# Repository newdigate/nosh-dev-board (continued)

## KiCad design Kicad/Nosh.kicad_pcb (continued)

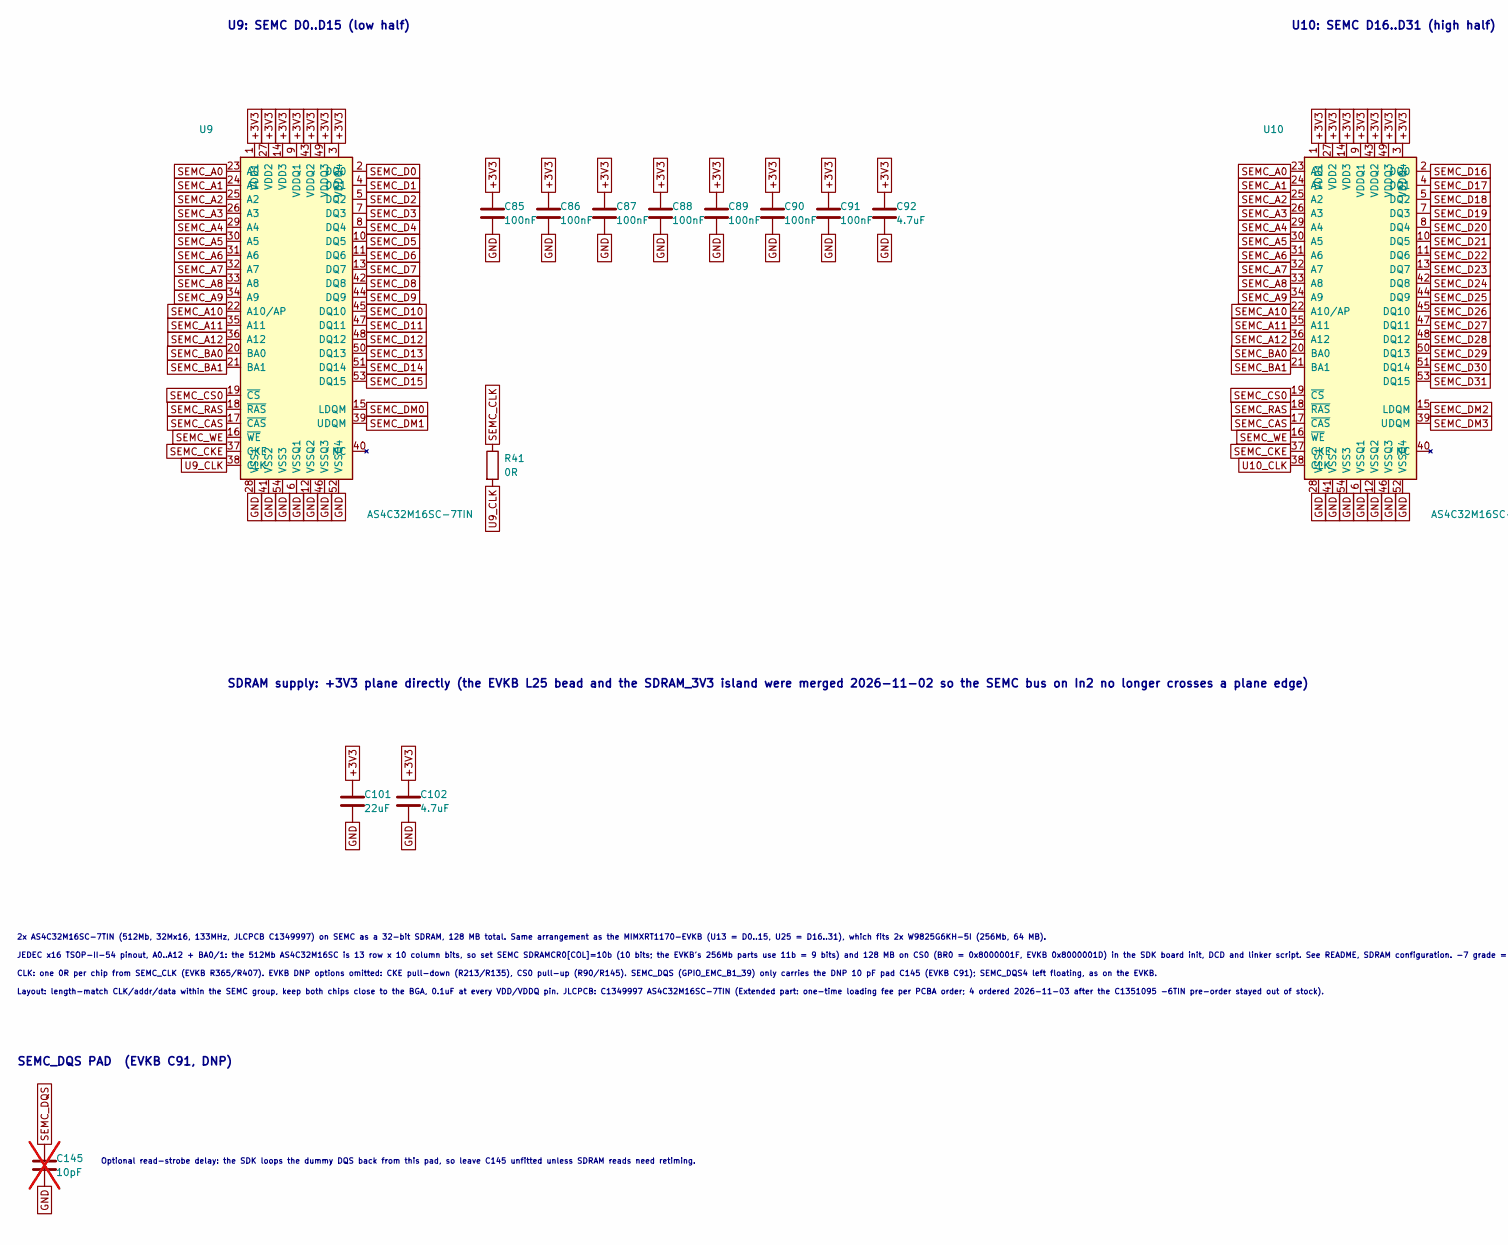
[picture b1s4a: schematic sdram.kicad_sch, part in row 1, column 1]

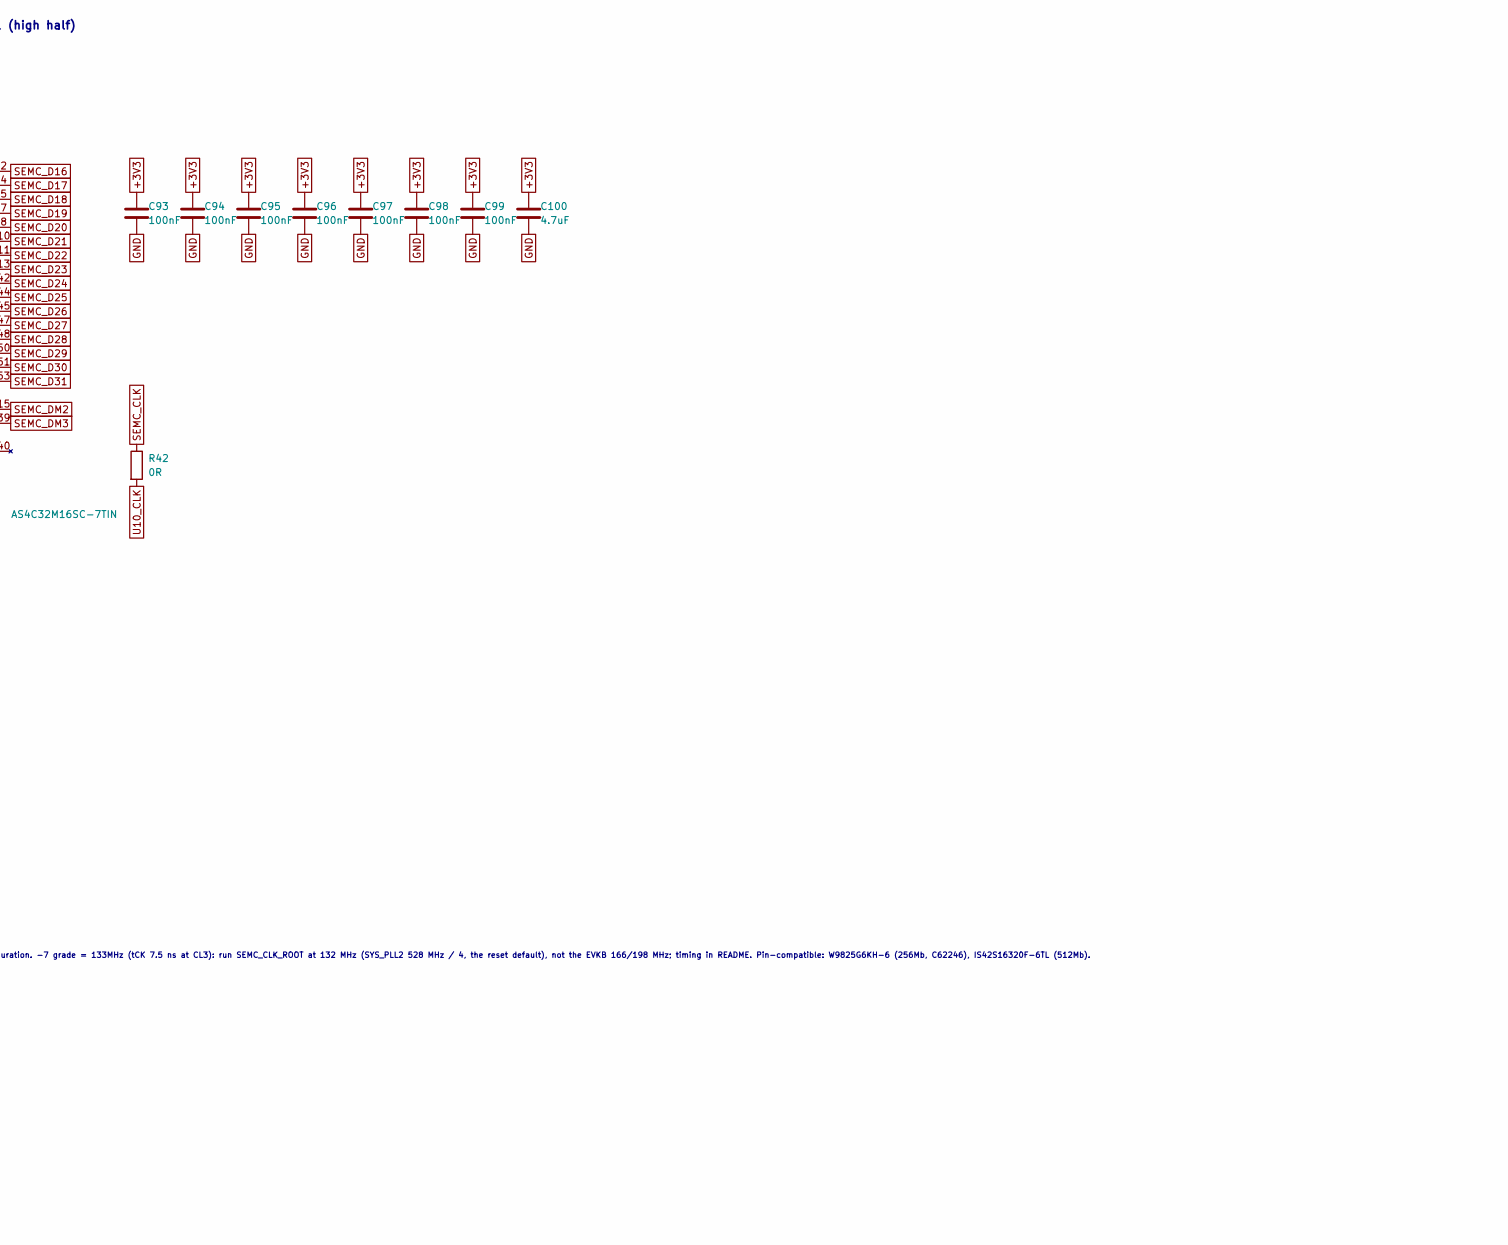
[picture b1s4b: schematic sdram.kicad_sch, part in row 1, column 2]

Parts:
C85, C86, C87, C88, C89, C90, C91, C94, C95, C96, C97, C98, C99: 100nF; C_0402_1005Metric_JLC; MPN CL05B104KO5NNNC; LCSC C1525
C92, C100, C102: 4.7uF; C_0603_1608Metric; MPN CL10A475KO8NNNC; LCSC C19666
C93: 100nF; C_0402_1005Metric_ViP; MPN CL05B104KO5NNNC; LCSC C1525
C101: 22uF; C_0805_2012Metric; MPN CL21A226MAQNNNE; LCSC C45783
C145: 10pF; C_0402_1005Metric_JLC; MPN 0402CG100J500NT; LCSC C1545; not fitted
R41, R42: 0R; R_0402_1005Metric_JLC; MPN 0402WGF0000TCE; LCSC C17168
U9, U10: AS4C32M16SC-7TIN; TSOP-II-54_22.2x10.16mm_P0.8mm; MPN AS4C32M16SC-7TIN; LCSC C1349997

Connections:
+3V3: C85.1, C86.1, C87.1, C88.1, C89.1, C90.1, C91.1, C92.1, C93.1, C94.1, C95.1, C96.1, C97.1, C98.1, C99.1, C100.1, C101.1, C102.1, U9.1 (VDD1), U9.3 (VDDQ4), U9.9 (VDDQ1), U9.14 (VDD3), U9.27 (VDD2), U9.43 (VDDQ2), U9.49 (VDDQ3), U10.1 (VDD1), U10.3 (VDDQ4), U10.9 (VDDQ1), U10.14 (VDD3), U10.27 (VDD2), U10.43 (VDDQ2), U10.49 (VDDQ3); also elsewhere on the board
GND: C85.2, C86.2, C87.2, C88.2, C89.2, C90.2, C91.2, C92.2, C93.2, C94.2, C95.2, C96.2, C97.2, C98.2, C99.2, C100.2, C101.2, C102.2, C145.2, U9.6 (VSSQ1), U9.12 (VSSQ2), U9.28 (VSS1), U9.41 (VSS2), U9.46 (VSSQ3), U9.52 (VSSQ4), U9.54 (VSS3), U10.6 (VSSQ1), U10.12 (VSSQ2), U10.28 (VSS1), U10.41 (VSS2), U10.46 (VSSQ3), U10.52 (VSSQ4), U10.54 (VSS3); also elsewhere on the board
SEMC_A0: U9.23 (A0), U10.23 (A0); also elsewhere on the board
SEMC_A1: U9.24 (A1), U10.24 (A1); also elsewhere on the board
SEMC_A2: U9.25 (A2), U10.25 (A2); also elsewhere on the board
SEMC_A3: U9.26 (A3), U10.26 (A3); also elsewhere on the board
SEMC_A4: U9.29 (A4), U10.29 (A4); also elsewhere on the board
SEMC_A5: U9.30 (A5), U10.30 (A5); also elsewhere on the board
SEMC_A6: U9.31 (A6), U10.31 (A6); also elsewhere on the board
SEMC_A7: U9.32 (A7), U10.32 (A7); also elsewhere on the board
SEMC_A8: U9.33 (A8), U10.33 (A8); also elsewhere on the board
SEMC_A9: U9.34 (A9), U10.34 (A9); also elsewhere on the board
SEMC_A10: U9.22 (A10/AP), U10.22 (A10/AP); also elsewhere on the board
SEMC_A11: U9.35 (A11), U10.35 (A11); also elsewhere on the board
SEMC_A12: U9.36 (A12), U10.36 (A12); also elsewhere on the board
SEMC_BA0: U9.20 (BA0), U10.20 (BA0); also elsewhere on the board
SEMC_BA1: U9.21 (BA1), U10.21 (BA1); also elsewhere on the board
SEMC_CAS: U9.17 (~CAS), U10.17 (~CAS); also elsewhere on the board
SEMC_CKE: U9.37 (CKE), U10.37 (CKE); also elsewhere on the board
SEMC_CLK: R41.1, R42.1; also elsewhere on the board
SEMC_CS0: U9.19 (~CS), U10.19 (~CS); also elsewhere on the board
SEMC_D0: U9.2 (DQ0); also elsewhere on the board
SEMC_D1: U9.4 (DQ1); also elsewhere on the board
SEMC_D2: U9.5 (DQ2); also elsewhere on the board
SEMC_D3: U9.7 (DQ3); also elsewhere on the board
SEMC_D4: U9.8 (DQ4); also elsewhere on the board
SEMC_D5: U9.10 (DQ5); also elsewhere on the board
SEMC_D6: U9.11 (DQ6); also elsewhere on the board
SEMC_D7: U9.13 (DQ7); also elsewhere on the board
SEMC_D8: U9.42 (DQ8); also elsewhere on the board
SEMC_D9: U9.44 (DQ9); also elsewhere on the board
SEMC_D10: U9.45 (DQ10); also elsewhere on the board
SEMC_D11: U9.47 (DQ11); also elsewhere on the board
SEMC_D12: U9.48 (DQ12); also elsewhere on the board
SEMC_D13: U9.50 (DQ13); also elsewhere on the board
SEMC_D14: U9.51 (DQ14); also elsewhere on the board
SEMC_D15: U9.53 (DQ15); also elsewhere on the board
SEMC_D16: U10.2 (DQ0); also elsewhere on the board
SEMC_D17: U10.4 (DQ1); also elsewhere on the board
SEMC_D18: U10.5 (DQ2); also elsewhere on the board
SEMC_D19: U10.7 (DQ3); also elsewhere on the board
SEMC_D20: U10.8 (DQ4); also elsewhere on the board
SEMC_D21: U10.10 (DQ5); also elsewhere on the board
SEMC_D22: U10.11 (DQ6); also elsewhere on the board
SEMC_D23: U10.13 (DQ7); also elsewhere on the board
SEMC_D24: U10.42 (DQ8); also elsewhere on the board
SEMC_D25: U10.44 (DQ9); also elsewhere on the board
SEMC_D26: U10.45 (DQ10); also elsewhere on the board
SEMC_D27: U10.47 (DQ11); also elsewhere on the board
SEMC_D28: U10.48 (DQ12); also elsewhere on the board
SEMC_D29: U10.50 (DQ13); also elsewhere on the board
SEMC_D30: U10.51 (DQ14); also elsewhere on the board
SEMC_D31: U10.53 (DQ15); also elsewhere on the board
SEMC_DM0: U9.15 (LDQM); also elsewhere on the board
SEMC_DM1: U9.39 (UDQM); also elsewhere on the board
SEMC_DM2: U10.15 (LDQM); also elsewhere on the board
SEMC_DM3: U10.39 (UDQM); also elsewhere on the board
SEMC_DQS: C145.1; also elsewhere on the board
SEMC_RAS: U9.18 (~RAS), U10.18 (~RAS); also elsewhere on the board
SEMC_WE: U9.16 (~WE), U10.16 (~WE); also elsewhere on the board
U9_CLK: R41.2, U9.38 (CLK)
U10_CLK: R42.2, U10.38 (CLK)

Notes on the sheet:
SDRAM supply: +3V3 plane directly (the EVKB L25 bead and the SDRAM_3V3 island were merged 2026-11-02 so the SEMC bus on In2 no longer crosses a plane edge)
SEMC_DQS PAD (EVKB C91, DNP)
Layout: length-match CLK/addr/data within the SEMC group, keep both chips close to the BGA, 0.1uF at every VDD/VDDQ pin. JLCPCB: C1349997 AS4C32M16SC-7TIN (Extended part: one-time loading fee per PCBA order; 4 ordered 2026-11-03 after the C1351095 -6TIN pre-order stayed out of stock).
U9: SEMC D0..D15 (low half)
CLK: one 0R per chip from SEMC_CLK (EVKB R365/R407). EVKB DNP options omitted: CKE pull-down (R213/R135), CS0 pull-up (R90/R145). SEMC_DQS (GPIO_EMC_B1_39) only carries the DNP 10 pF pad C145 (EVKB C91); SEMC_DQS4 left floating, as on the EVKB.
JEDEC x16 TSOP-II-54 pinout, A0..A12 + BA0/1: the 512Mb AS4C32M16SC is 13 row x 10 column bits, so set SEMC SDRAMCR0[COL]=10b (10 bits; the EVKB's 256Mb parts use 11b = 9 bits) and 128 MB on CS0 (BR0 = 0x8000001F, EVKB 0x8000001D) in the SDK board init, DCD and linker script. See README, SDRAM conf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
U10: SEMC D16..D31 (high half)
2x AS4C32M16SC-7TIN (512Mb, 32Mx16, 133MHz, JLCPCB C1349997) on SEMC as a 32-bit SDRAM, 128 MB total. Same arrangement as the MIMXRT1170-EVKB (U13 = D0..15, U25 = D16..31), which fits 2x W9825G6KH-5I (256Mb, 64 MB).
Optional read-strobe delay: the SDK loops the dummy DQS back from this pad, so leave C145 unfitted unless SDRAM reads need retiming.

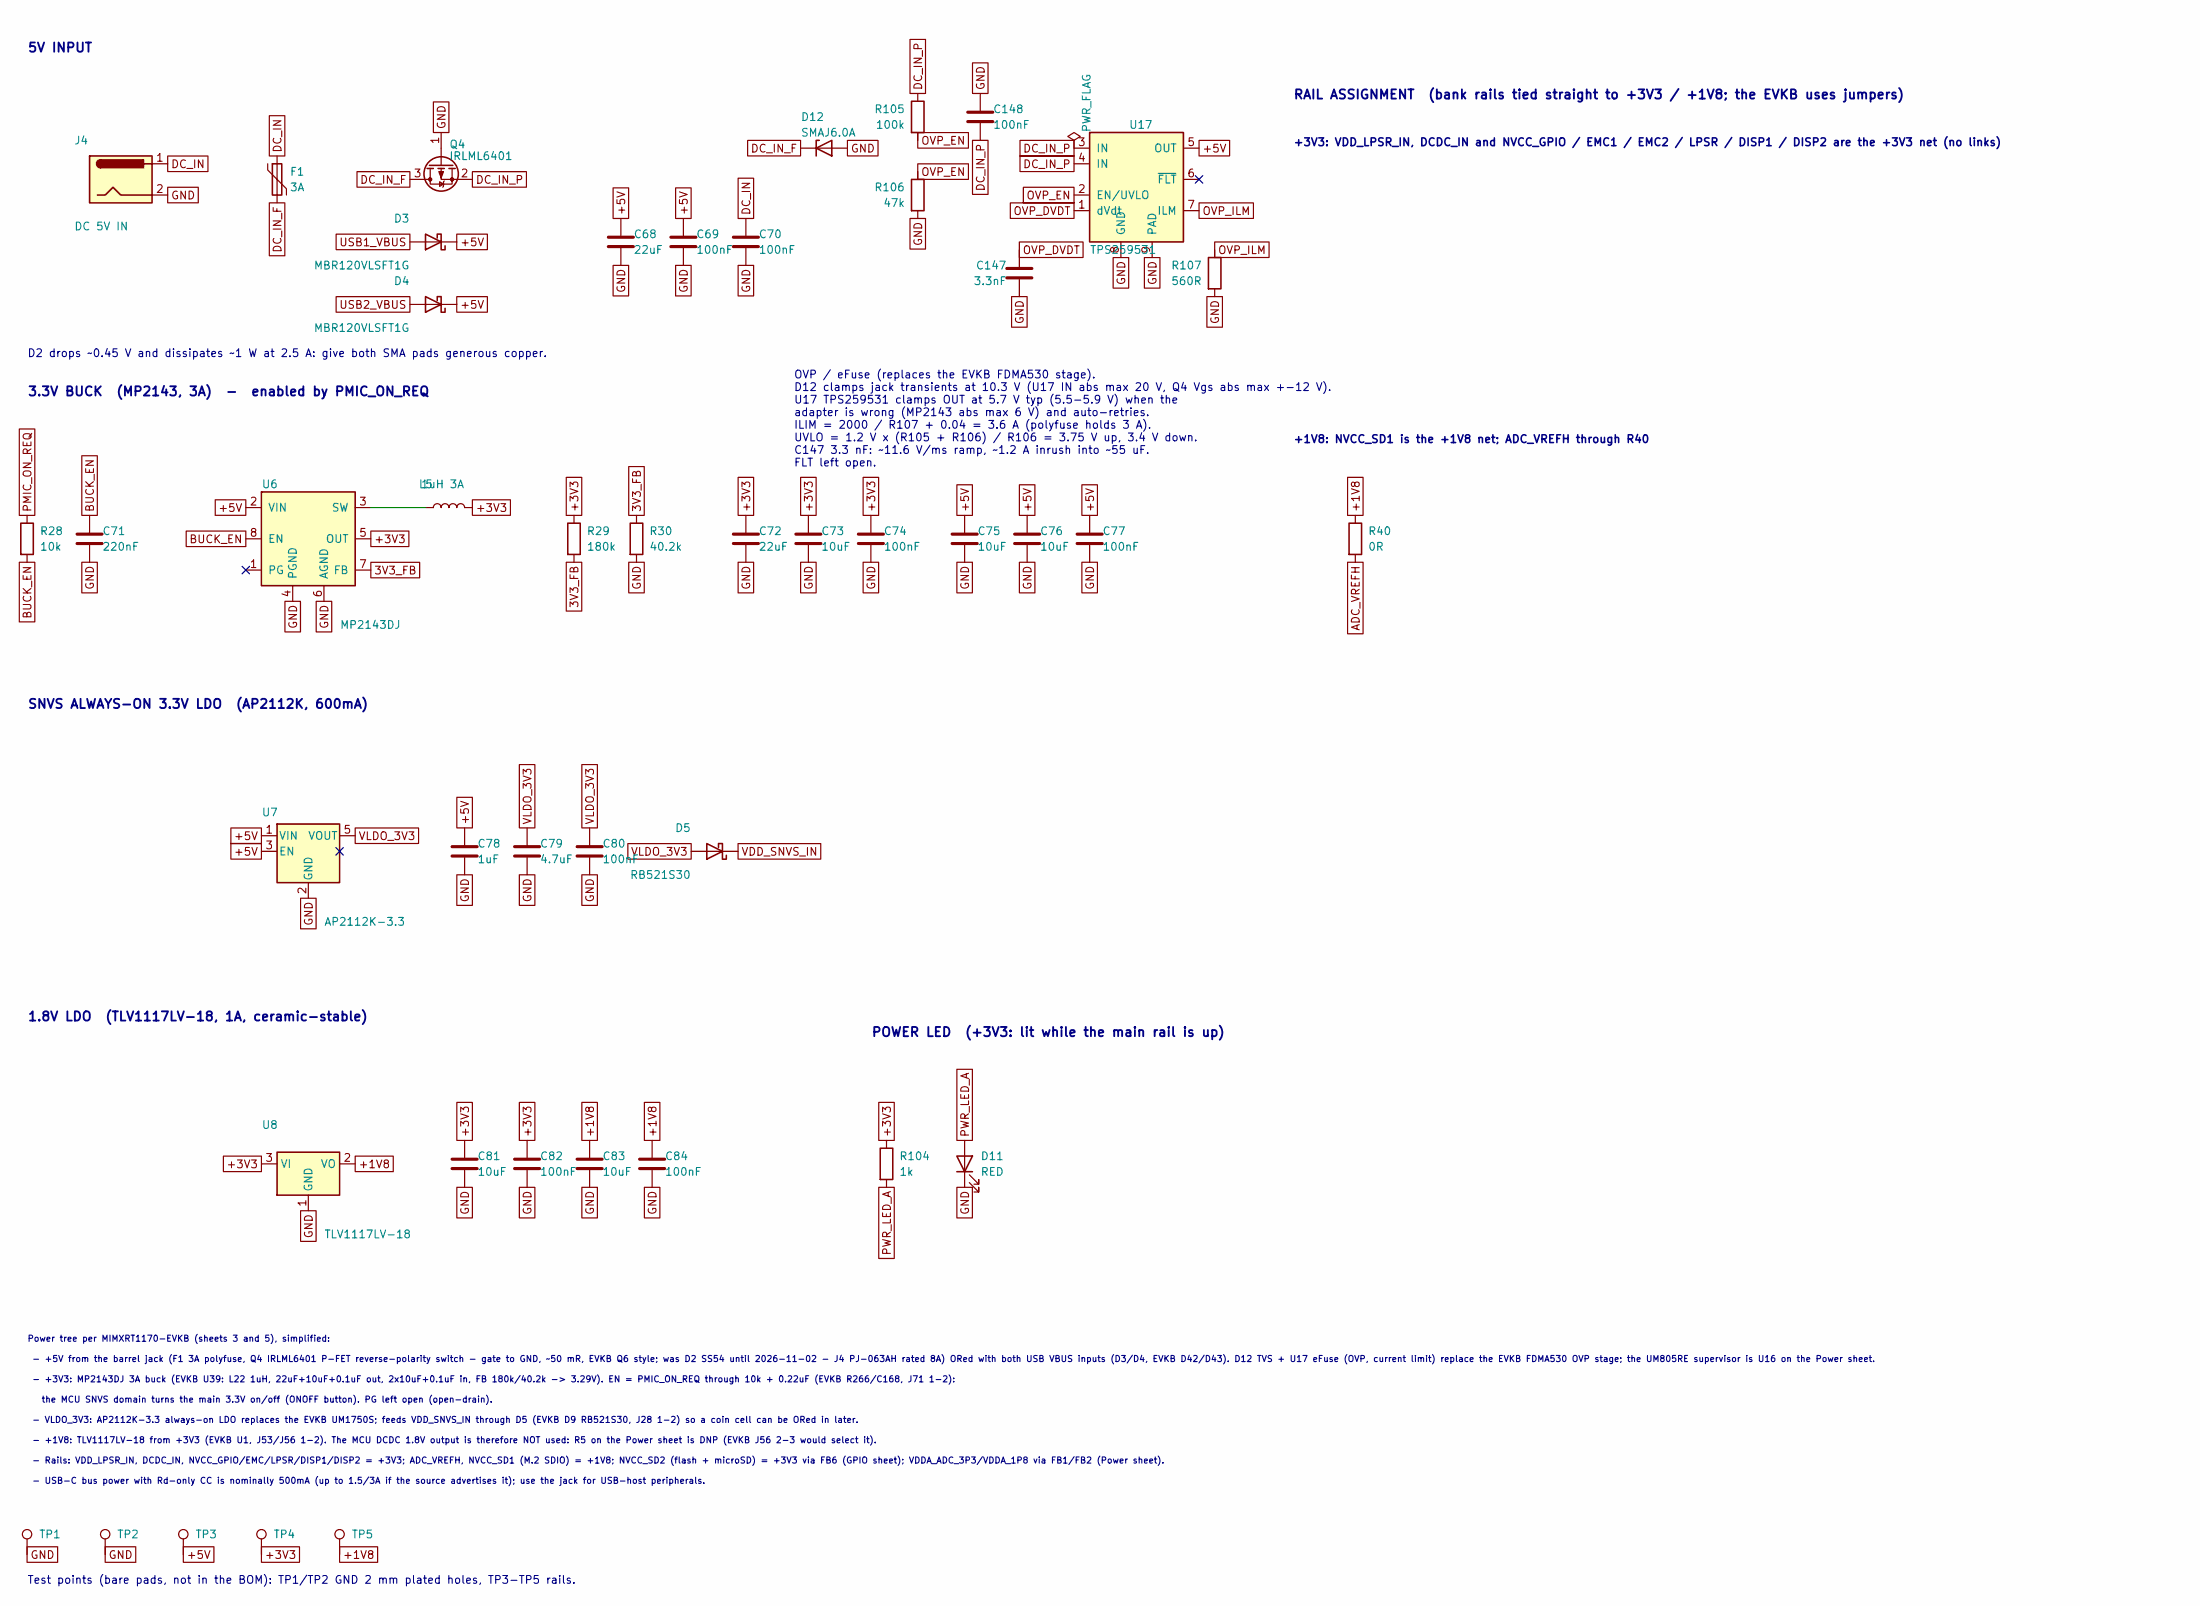
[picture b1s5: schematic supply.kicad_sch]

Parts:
C68, C72: 22uF; C_0805_2012Metric; MPN CL21A226MAQNNNE; LCSC C45783
C69, C70, C74, C77, C80, C82, C84, C148: 100nF; C_0402_1005Metric_JLC; MPN CL05B104KO5NNNC; LCSC C1525
C71: 220nF; C_0402_1005Metric_JLC; MPN CL05B224KO5NNNC; LCSC C16772
C73, C75, C76, C81, C83: 10uF; C_0603_1608Metric; MPN CL10A106KP8NNNC; LCSC C19702
C78: 1uF; C_0402_1005Metric_JLC; MPN CL05A105KA5NQNC; LCSC C52923
C79: 4.7uF; C_0603_1608Metric; MPN CL10A475KO8NNNC; LCSC C19666
C147: 3.3nF; C_0603_1608Metric; MPN CL10B332KB8NNNC; LCSC C1613
D3, D4: MBR120VLSFT1G; D_SOD-123F; MPN MBR120VLSFT1G; LCSC C223608
D5: RB521S30; D_SOD-523; MPN RB521S30T1G; LCSC C145179
D11: RED; LED_0603_1608Metric; MPN KT-0603R; LCSC C2286
D12: SMAJ6.0A; D_SMA; MPN SMAJ6.0A; LCSC C223993
F1: 3A; Fuse_1812_4532Metric; MPN SMD1812P300SLR/24; LCSC C2892380
J4: DC 5V IN; BarrelJack_CUI_PJ-063AH_Horizontal_JLC; MPN PJ-063AH; LCSC C22434582
L5: 1uH 3A; L_APV_ANR4020; MPN SWPA4020S1R0NT; LCSC C91254
Q4: IRLML6401; SOT-23; MPN IRLML6401TRPBF; LCSC C3034
R28: 10k; R_0402_1005Metric_JLC; MPN 0402WGF1002TCE; LCSC C25744
R29: 180k; R_0402_1005Metric_JLC; MPN 0402WGF1803TCE; LCSC C25760
R30: 40.2k; R_0402_1005Metric_JLC; MPN 0402WGF4022TCE; LCSC C25893
R40: 0R; R_0603_1608Metric; MPN 0603WAF0000T5E; LCSC C21189
R104: 1k; R_0402_1005Metric_JLC; MPN 0402WGF1001TCE; LCSC C11702
R105: 100k; R_0402_1005Metric_JLC; MPN 0402WGF1003TCE; LCSC C25741
R106: 47k; R_0402_1005Metric_JLC; MPN 0402WGF4702TCE; LCSC C25792
R107: 560R; R_0402_1005Metric_JLC; MPN 0402WGF5600TCE; LCSC C25126
TP1, TP2: TestPoint; TestPoint_THTPad_D2.0mm_Drill1.0mm_JLC
TP3, TP4, TP5: TestPoint; TestPoint_Pad_D1.0mm_JLC
U6: MP2143DJ; TSOT-23-8; MPN MP2143DJ-LF-Z; LCSC C43427
U7: AP2112K-3.3; SOT-23-5; MPN AP2112K-3.3TRG1; LCSC C51118
U8: TLV1117LV-18; SOT-223-3_TabPin2; MPN TLV1117LV18DCYR; LCSC C80105
U17: TPS259531; Texas_DSG0008A_WSON-8-1EP_2x2mm_P0.5mm_EP0.9x1.6mm; MPN TPS259531DSGR; LCSC C2155674

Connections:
3V3_FB: R29.2, R30.1, U6.7 (FB)
+1V8: C83.1, C84.1, R40.1, TP5.1, U8.2 (VO); also elsewhere on the board
+3V3: C72.1, C73.1, C74.1, C81.1, C82.1, L5.2, R29.1, R104.1, TP4.1, U6.5 (OUT), U8.3 (VI); also elsewhere on the board
+5V: C68.1, C69.1, C75.1, C76.1, C77.1, C78.1, D3.1 (K), D4.1 (K), TP3.1, U6.2 (VIN), U7.1 (VIN), U7.3 (EN), U17.5 (OUT); also elsewhere on the board
ADC_VREFH: R40.2; also elsewhere on the board
BUCK_EN: C71.1, R28.2, U6.8 (EN)
DC_IN: C70.1, F1.1, J4.1
DC_IN_F: D12.1 (K), F1.2, Q4.3 (D)
DC_IN_P: C148.2, Q4.2 (S), R105.1, U17.3 (IN), U17.4 (IN)
GND: C68.2, C69.2, C70.2, C71.2, C72.2, C73.2, C74.2, C75.2, C76.2, C77.2, C78.2, C79.2, C80.2, C81.2, C82.2, C83.2, C84.2, C147.2, C148.1, D11.1 (K), D12.2 (A), J4.2, Q4.1 (G), R30.2, R106.2, R107.2, TP1.1, TP2.1, U6.4 (PGND), U6.6 (AGND), U7.2 (GND), U8.1 (GND), U17.8 (GND), U17.9 (PAD); also elsewhere on the board
unnamed: L5.1, U6.3 (SW)
OVP_DVDT: C147.1, U17.1 (dVdt)
OVP_EN: R105.2, R106.1, U17.2 (EN/UVLO)
OVP_ILM: R107.1, U17.7 (ILM)
PMIC_ON_REQ: R28.1; also elsewhere on the board
PWR_LED_A: D11.2 (A), R104.2
USB1_VBUS: D3.2 (A); also elsewhere on the board
USB2_VBUS: D4.2 (A); also elsewhere on the board
VDD_SNVS_IN: D5.1 (K); also elsewhere on the board
VLDO_3V3: C79.1, C80.1, D5.2 (A), U7.5 (VOUT)

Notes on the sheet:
- +5V from the barrel jack (F1 3A polyfuse, Q4 IRLML6401 P-FET reverse-polarity switch - gate to GND, ~50 mR, EVKB Q6 style; was D2 SS54 until 2026-11-02 - J4 PJ-063AH rated 8A) ORed with both USB VBUS inputs (D3/D4, EVKB D42/D43). D12 TVS + U17 eFuse (OVP, current limit) replace the EVKB FDMA530 O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
+1V8: NVCC_SD1 is the +1V8 net; ADC_VREFH through R40
5V INPUT
- USB-C bus power with Rd-only CC is nominally 500mA (up to 1.5/3A if the source advertises it); use the jack for USB-host peripherals.
D2 drops ~0.45 V and dissipates ~1 W at 2.5 A: give both SMA pads generous copper.
RAIL ASSIGNMENT (bank rails tied straight to +3V3 / +1V8; the EVKB uses jumpers)
SNVS ALWAYS-ON 3.3V LDO (AP2112K, 600mA)
- +3V3: MP2143DJ 3A buck (EVKB U39: L22 1uH, 22uF+10uF+0.1uF out, 2x10uF+0.1uF in, FB 180k/40.2k -> 3.29V). EN = PMIC_ON_REQ through 10k + 0.22uF (EVKB R266/C168, J71 1-2):
Power tree per MIMXRT1170-EVKB (sheets 3 and 5), simplified:
- VLDO_3V3: AP2112K-3.3 always-on LDO replaces the EVKB UM1750S; feeds VDD_SNVS_IN through D5 (EVKB D9 RB521S30, J28 1-2) so a coin cell can be ORed in later.
POWER LED (+3V3: lit while the main rail is up)
1.8V LDO (TLV1117LV-18, 1A, ceramic-stable)
3.3V BUCK (MP2143, 3A) - enabled by PMIC_ON_REQ
the MCU SNVS domain turns the main 3.3V on/off (ONOFF button). PG left open (open-drain).
+3V3: VDD_LPSR_IN, DCDC_IN and NVCC_GPIO / EMC1 / EMC2 / LPSR / DISP1 / DISP2 are the +3V3 net (no links)
- Rails: VDD_LPSR_IN, DCDC_IN, NVCC_GPIO/EMC/LPSR/DISP1/DISP2 = +3V3; ADC_VREFH, NVCC_SD1 (M.2 SDIO) = +1V8; NVCC_SD2 (flash + microSD) = +3V3 via FB6 (GPIO sheet); VDDA_ADC_3P3/VDDA_1P8 via FB1/FB2 (Power sheet).
- +1V8: TLV1117LV-18 from +3V3 (EVKB U1, J53/J56 1-2). The MCU DCDC 1.8V output is therefore NOT used: R5 on the Power sheet is DNP (EVKB J56 2-3 would select it).
OVP / eFuse (replaces the EVKB FDMA530 stage). D12 clamps jack transients at 10.3 V (U17 IN abs max 20 V, Q4 Vgs abs max +-12 V). U17 TPS259531 clamps OUT at 5.7 V typ (5.5-5.9 V) when the adapter is wrong (MP2143 abs max 6 V) and auto-retries. ILIM = 2000 / R107 + 0.04 = 3.6 A (polyfuse holds 3 A)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
Test points (bare pads, not in the BOM): TP1/TP2 GND 2 mm plated holes, TP3-TP5 rails.

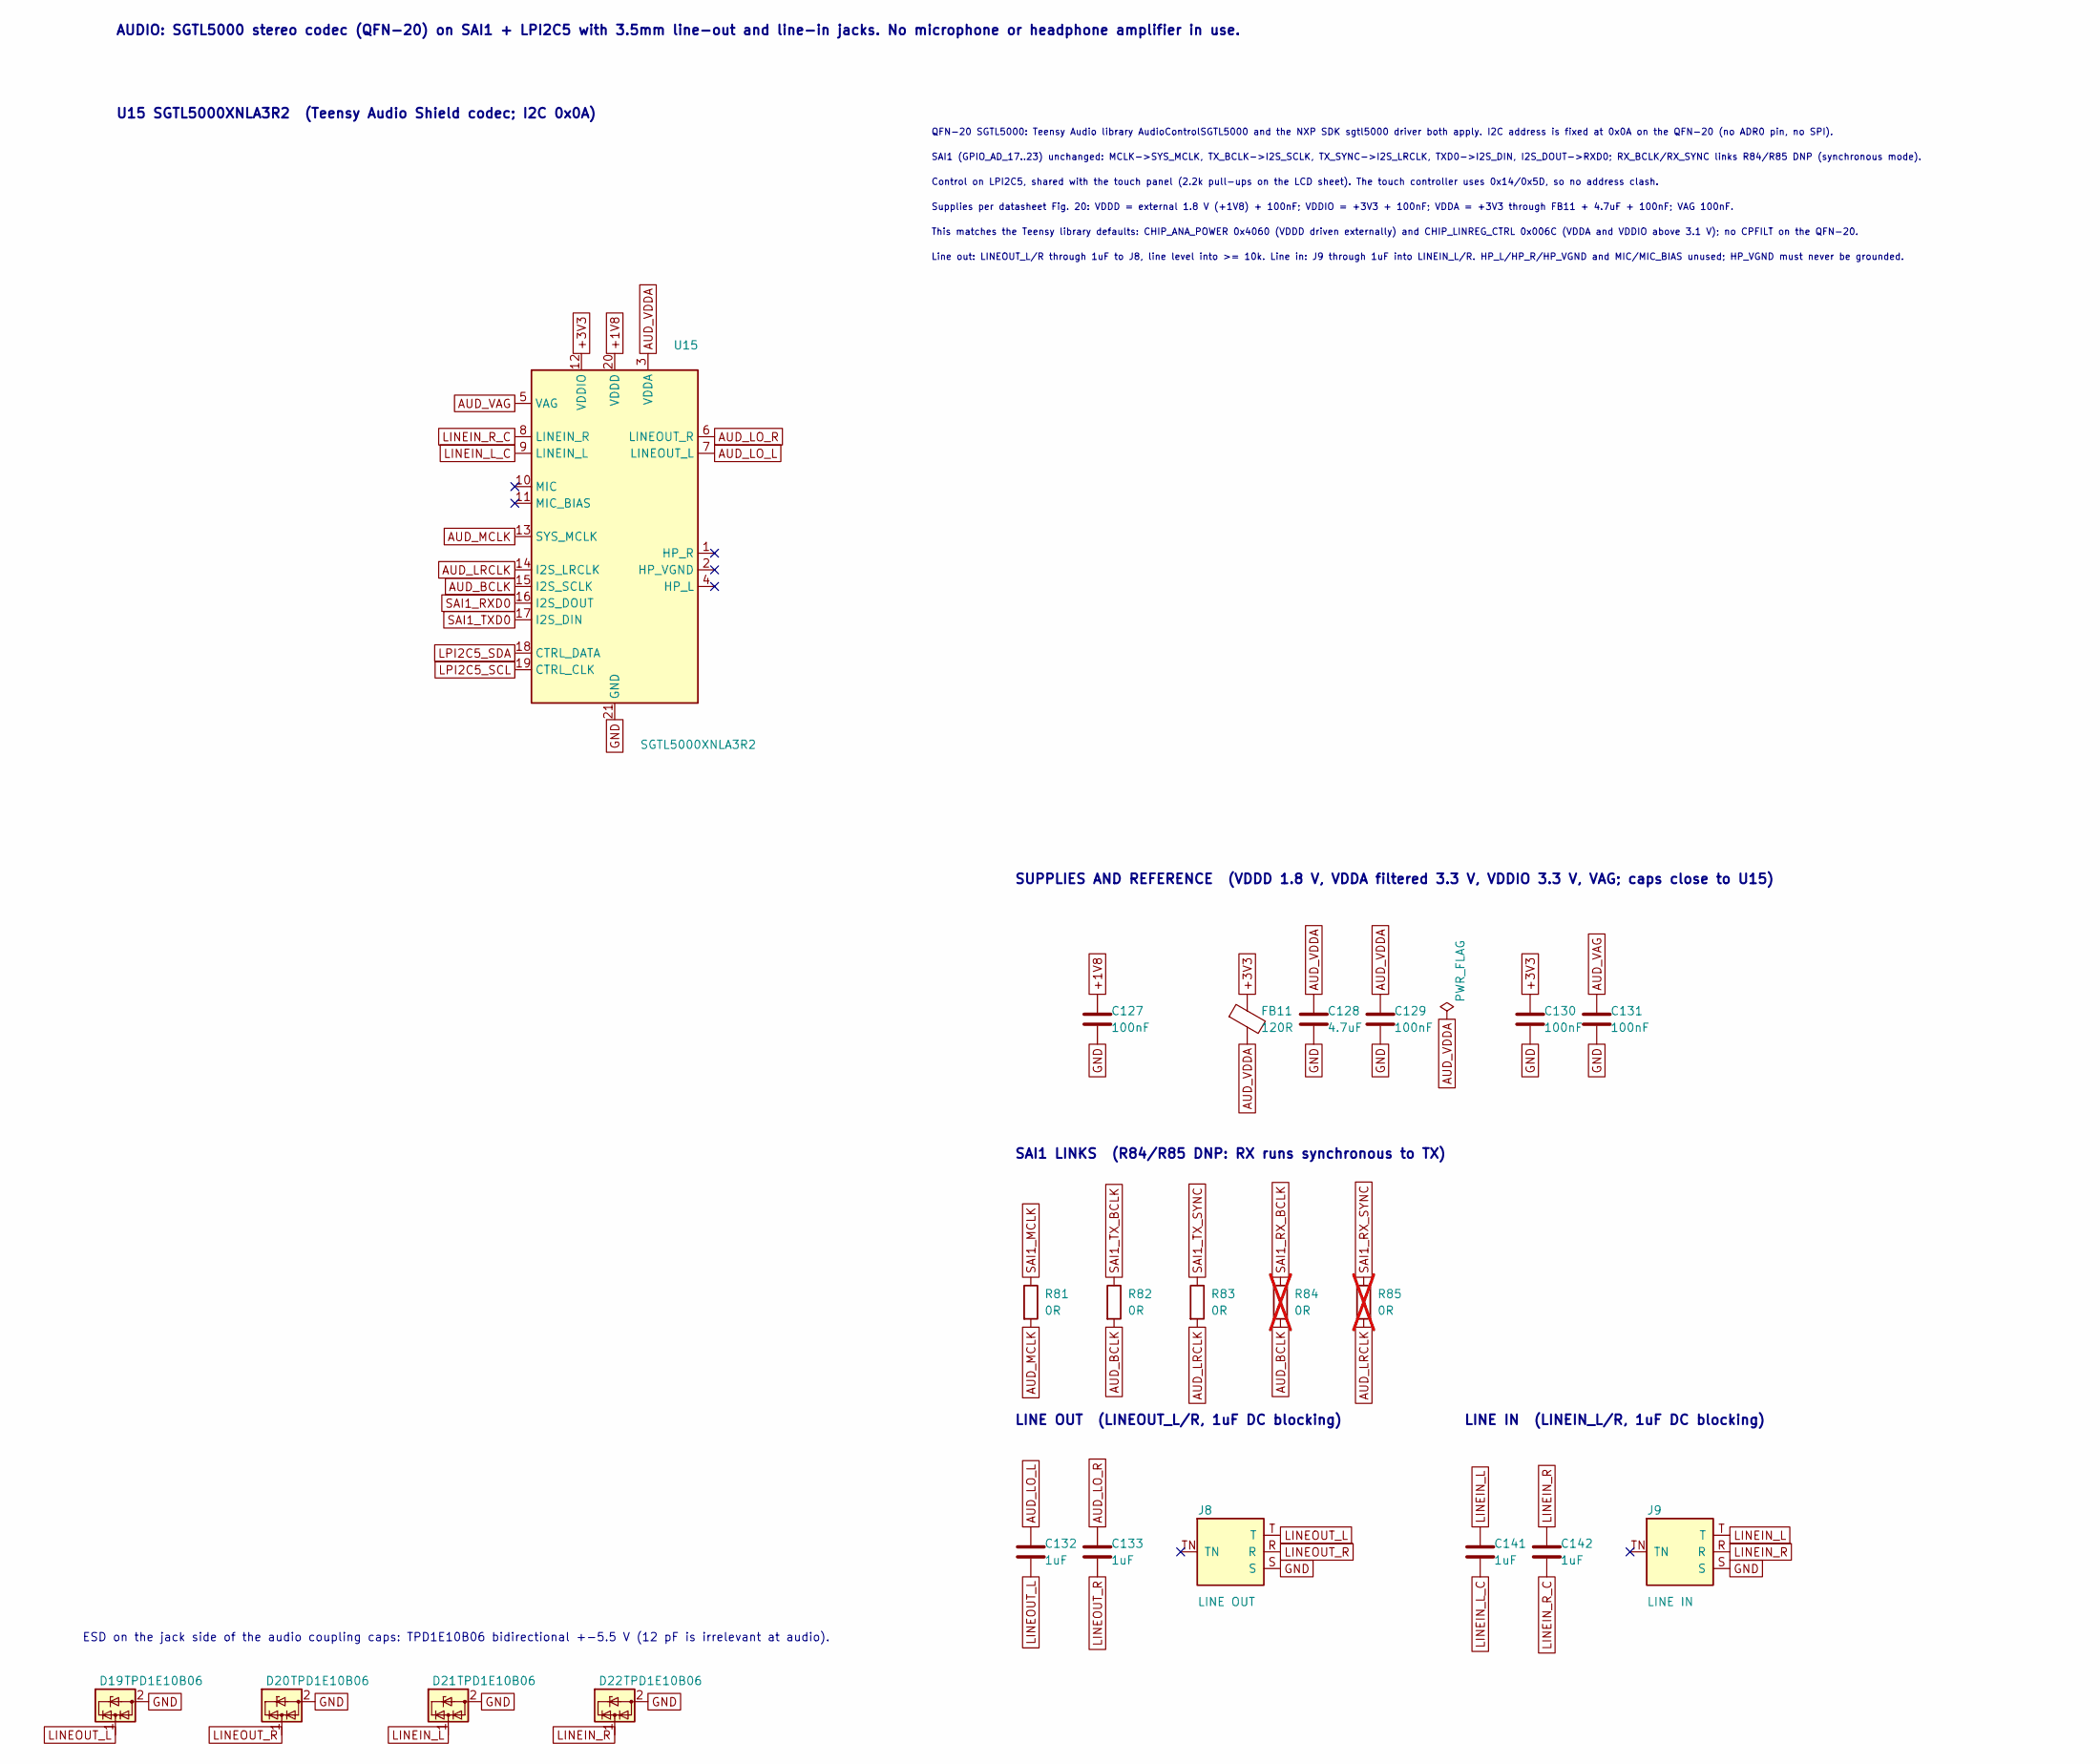
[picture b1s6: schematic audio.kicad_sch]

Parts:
C127, C129, C130, C131: 100nF; C_0402_1005Metric_JLC; MPN CL05B104KO5NNNC; LCSC C1525
C128: 4.7uF; C_0402_1005Metric_JLC; MPN CL05A475MP5NRNC; LCSC C23733
C132, C133, C141, C142: 1uF; C_0402_1005Metric_JLC; MPN CL05A105KA5NQNC; LCSC C52923
D19, D20, D21, D22: TPD1E10B06; ESD_X1SON-2_0.6x1mm_JLC; MPN TPD1E10B06DPYR; LCSC C48260
FB11: 120R; L_0402_1005Metric; MPN BLM15AG121SN1D; LCSC C85812
J8: LINE OUT; Jack_3.5mm_CUI_SJ-3524-SMT_Horizontal_JLC; MPN SJ-3524-SMT-TR; LCSC C20182907
J9: LINE IN; Jack_3.5mm_CUI_SJ-3524-SMT_Horizontal_JLC; MPN SJ-3524-SMT-TR; LCSC C20182907
R81, R82, R83: 0R; R_0402_1005Metric_JLC; MPN 0402WGF0000TCE; LCSC C17168
R84, R85: 0R; R_0402_1005Metric_JLC; MPN 0402WGF0000TCE; LCSC C17168; not fitted
U15: SGTL5000XNLA3R2; QFN-20-1EP_3x3mm_P0.4mm_EP1.65x1.65mm; MPN SGTL5000XNLA3R2; LCSC C2651833

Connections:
+1V8: C127.1, U15.20 (VDDD); also elsewhere on the board
+3V3: C130.1, FB11.1, U15.12 (VDDIO); also elsewhere on the board
AUD_BCLK: R82.2, R84.2, U15.15 (I2S_SCLK)
AUD_LO_L: C132.1, U15.7 (LINEOUT_L)
AUD_LO_R: C133.1, U15.6 (LINEOUT_R)
AUD_LRCLK: R83.2, R85.2, U15.14 (I2S_LRCLK)
AUD_MCLK: R81.2, U15.13 (SYS_MCLK)
AUD_VAG: C131.1, U15.5 (VAG)
AUD_VDDA: C128.1, C129.1, FB11.2, U15.3 (VDDA)
GND: C127.2, C128.2, C129.2, C130.2, C131.2, D19.2 (GND), D20.2 (GND), D21.2 (GND), D22.2 (GND), J8.S, J9.S, U15.21 (GND); also elsewhere on the board
LINEIN_L: C141.1, D21.1 (I/O), J9.T
LINEIN_L_C: C141.2, U15.9 (LINEIN_L)
LINEIN_R: C142.1, D22.1 (I/O), J9.R
LINEIN_R_C: C142.2, U15.8 (LINEIN_R)
LINEOUT_L: C132.2, D19.1 (I/O), J8.T
LINEOUT_R: C133.2, D20.1 (I/O), J8.R
LPI2C5_SCL: U15.19 (CTRL_CLK); also elsewhere on the board
LPI2C5_SDA: U15.18 (CTRL_DATA); also elsewhere on the board
SAI1_MCLK: R81.1; also elsewhere on the board
SAI1_RXD0: U15.16 (I2S_DOUT); also elsewhere on the board
SAI1_RX_BCLK: R84.1; also elsewhere on the board
SAI1_RX_SYNC: R85.1; also elsewhere on the board
SAI1_TXD0: U15.17 (I2S_DIN); also elsewhere on the board
SAI1_TX_BCLK: R82.1; also elsewhere on the board
SAI1_TX_SYNC: R83.1; also elsewhere on the board

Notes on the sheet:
LINE OUT (LINEOUT_L/R, 1uF DC blocking)
Control on LPI2C5, shared with the touch panel (2.2k pull-ups on the LCD sheet). The touch controller uses 0x14/0x5D, so no address clash.
SAI1 LINKS (R84/R85 DNP: RX runs synchronous to TX)
SUPPLIES AND REFERENCE (VDDD 1.8 V, VDDA filtered 3.3 V, VDDIO 3.3 V, VAG; caps close to U15)
This matches the Teensy library defaults: CHIP_ANA_POWER 0x4060 (VDDD driven externally) and CHIP_LINREG_CTRL 0x006C (VDDA and VDDIO above 3.1 V); no CPFILT on the QFN-20.
LINE IN (LINEIN_L/R, 1uF DC blocking)
U15 SGTL5000XNLA3R2 (Teensy Audio Shield codec; I2C 0x0A)
Line out: LINEOUT_L/R through 1uF to J8, line level into >= 10k. Line in: J9 through 1uF into LINEIN_L/R. HP_L/HP_R/HP_VGND and MIC/MIC_BIAS unused; HP_VGND must never be grounded.
QFN-20 SGTL5000: Teensy Audio library AudioControlSGTL5000 and the NXP SDK sgtl5000 driver both apply. I2C address is fixed at 0x0A on the QFN-20 (no ADR0 pin, no SPI).
AUDIO: SGTL5000 stereo codec (QFN-20) on SAI1 + LPI2C5 with 3.5mm line-out and line-in jacks. No microphone or headphone amplifier in use.
Supplies per datasheet Fig. 20: VDDD = external 1.8 V (+1V8) + 100nF; VDDIO = +3V3 + 100nF; VDDA = +3V3 through FB11 + 4.7uF + 100nF; VAG 100nF.
SAI1 (GPIO_AD_17..23) unchanged: MCLK->SYS_MCLK, TX_BCLK->I2S_SCLK, TX_SYNC->I2S_LRCLK, TXD0->I2S_DIN, I2S_DOUT->RXD0; RX_BCLK/RX_SYNC links R84/R85 DNP (synchronous mode).
ESD on the jack side of the audio coupling caps: TPD1E10B06 bidirectional +-5.5 V (12 pF is irrelevant at audio).
